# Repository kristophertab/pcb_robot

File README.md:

# PCB do robota
Płytka z mcu, optoizolowanym połączeniem uart, połączeniem st-link, kilkoma poziomami zasilania. Ma za zadanie sterować odczytywać dane z enkoderów i sterować, przez mostki, pracą silników
### Schemat

### PCB
Górna warstwa:

Dolna warstwa:

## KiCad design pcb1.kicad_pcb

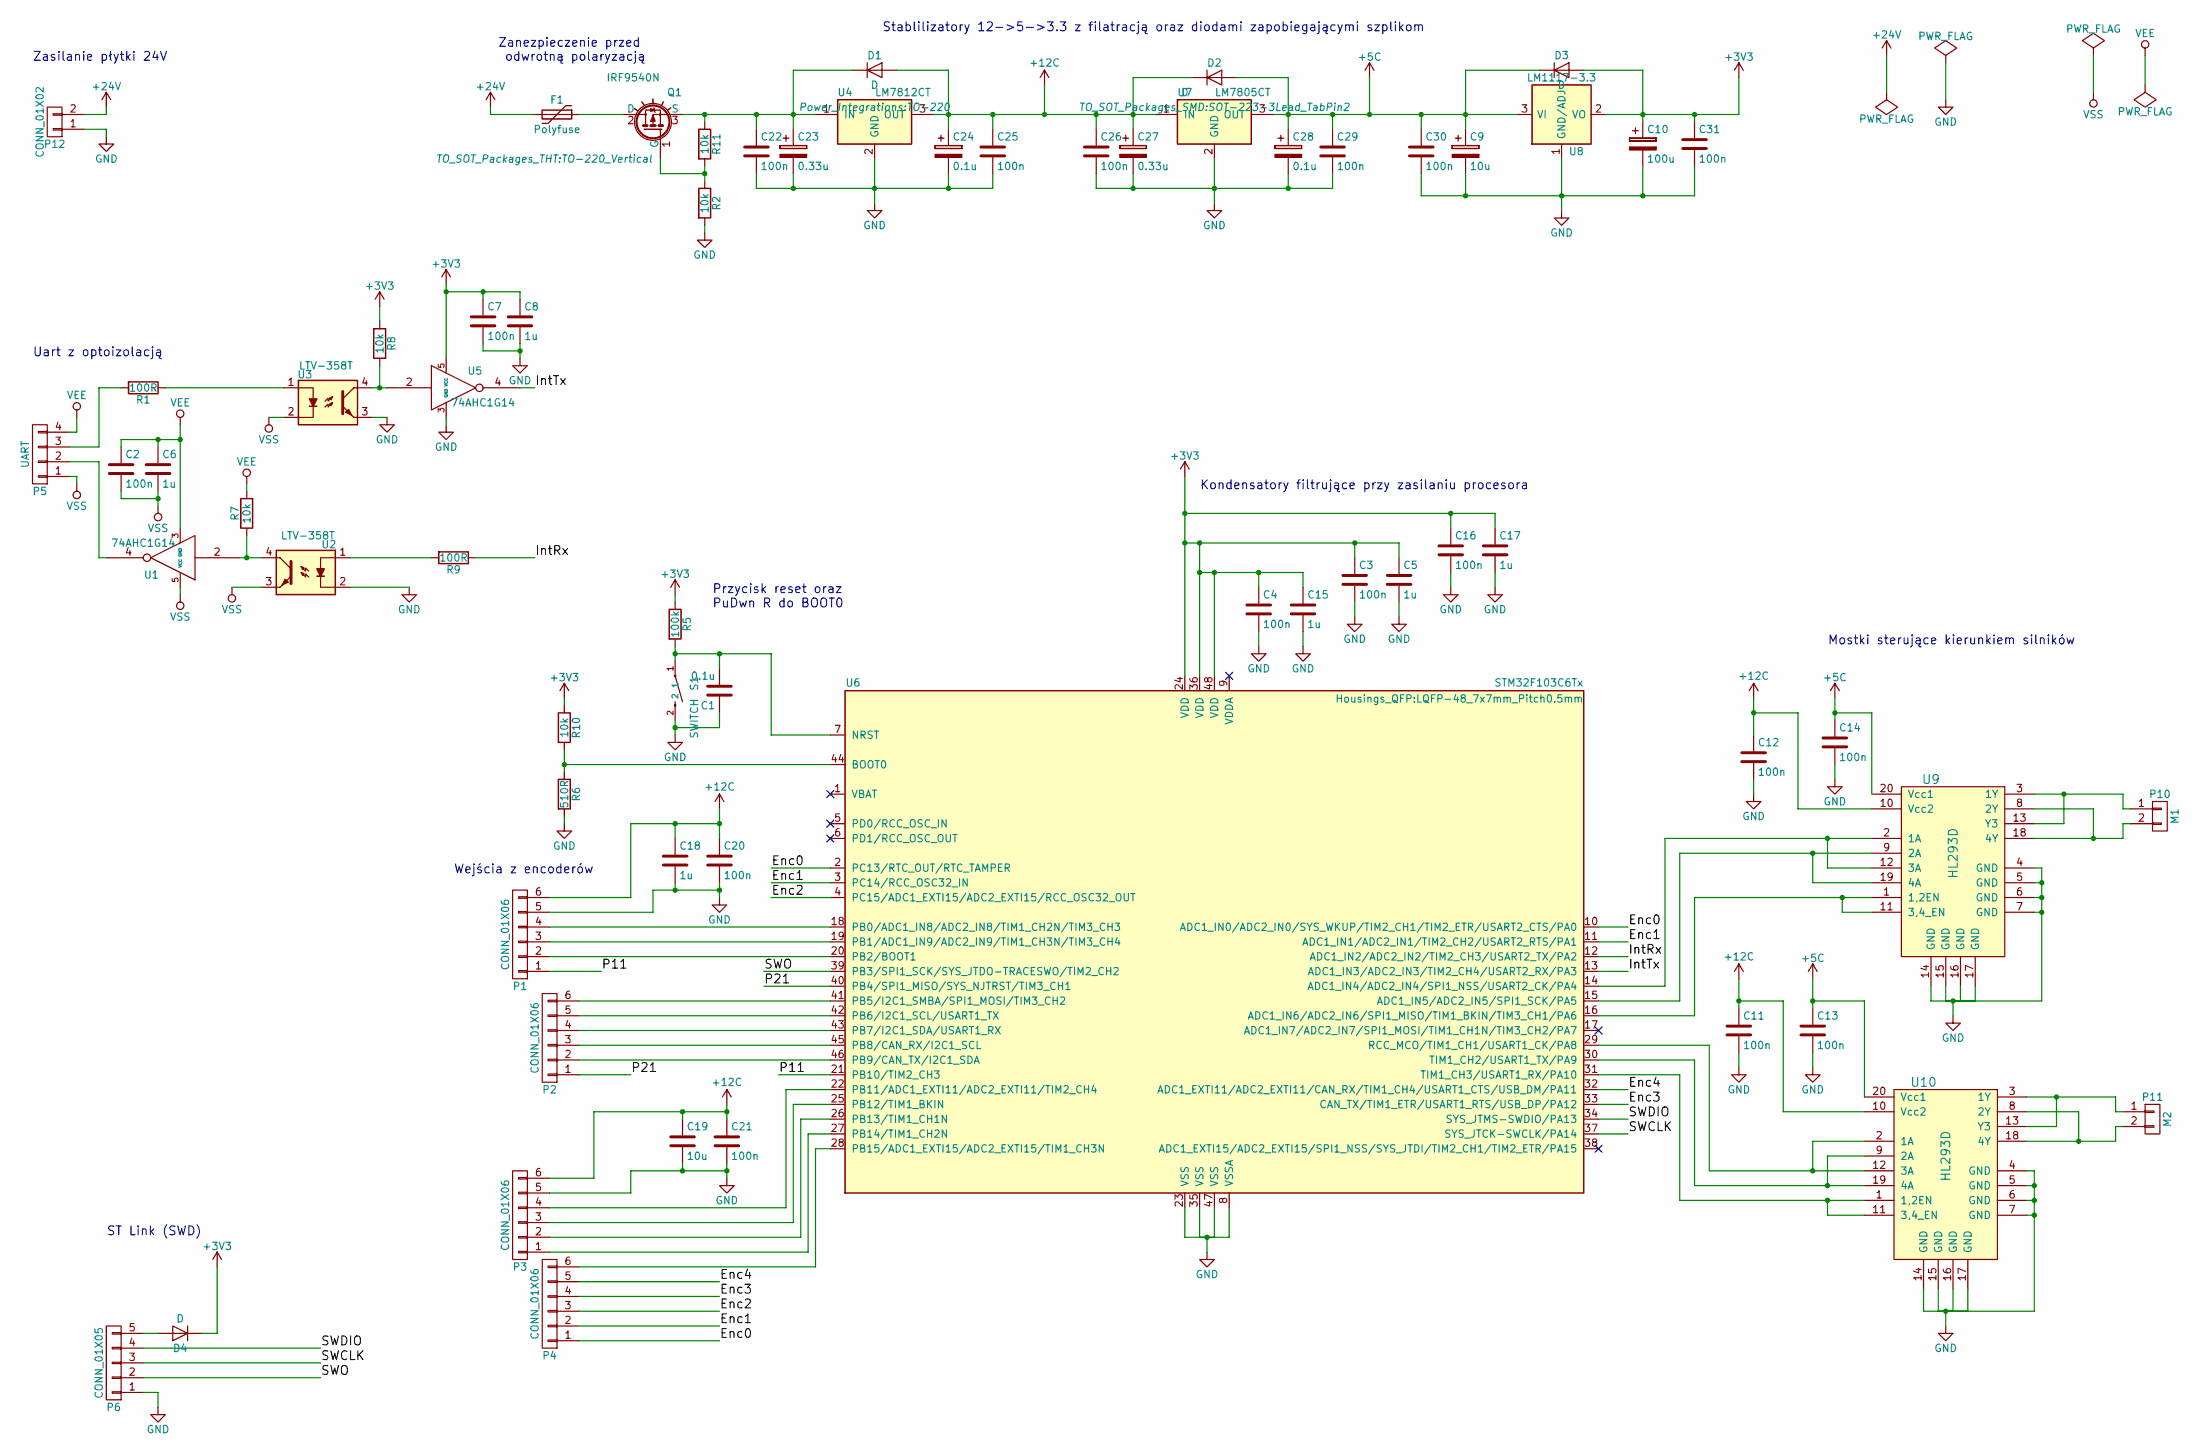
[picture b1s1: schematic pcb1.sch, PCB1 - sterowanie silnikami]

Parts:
C1, C24, C28: 0.1u; C_0805
C2, C3, C4, C7, C11, C12, C13, C14, C16, C20, C21, C22, C25, C26, C29, C30, C31: 100n; C_0805
C5, C6, C8, C15, C17, C18: 1u; C_0805
C9, C19: 10u; C_0805
C10: 100u; C_0805
C23, C27: 0.33u; C_0805
D1, D2, D3, D4: D; D_0805
F1: Polyfuse; SparkFun-PTC-1206
P1, P2, P3, P4: CONN_01X06; PINHEAD1-6
P5: UART; SparkFun-1X04
P6: CONN_01X05; SparkFun-1X05-1.27MM
P10: M1; bornier2
P11: M2; bornier2
P12: CONN_01X02; bornier2
Q1: IRF9540N; TO-220_Vertical
R1, R9: 100R; R_0805
R2, R7, R8, R10, R11: 10k; R_0805
R5: 100k; R_0805
R6: 510R; R_0805
S1: SWITCH; SW_SPST_TL3342
U1, U5: 74AHC1G14; SOT-353_SC-70-5
U2, U3: LTV-358T; SW_DIP_x2_W6.15mm_Slide_Omron_A6H
U4: LM7812CT; TO-220
U6: STM32F103C6Tx; LQFP-48_7x7mm_Pitch0.5mm
U7: LM7805CT; SOT-223-3Lead_TabPin2
U8: LM1117-3.3; SOT-223
U9, U10: HL293D; SOIC-20W_7.5x12.8mm_Pitch1.27mm

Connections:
+3V3: C3.1, C4.1, C5.1, C7.1, C8.1, C10.1, C15.1, C16.1, C17.1, C31.1, D3.2 (A), D4.1 (K), R5.1, R8.2, R10.1, U5.5 (VCC), U6.24 (VDD), U6.36 (VDD), U6.48 (VDD), U8.2 (VO), U8.4 (VO)
+5C: C9.1, C13.1, C14.1, C28.1, C29.1, C30.1, D2.2 (A), D3.1 (K), U7.3 (OUT), U8.3 (VI), U9.20 (Vcc1), U10.20 (Vcc1)
+12C: C11.1, C12.1, C18.1, C19.1, C20.1, C21.1, C24.1, C25.1, C26.1, C27.1, D1.2 (A), D2.1 (K), P1.6, P3.6, U4.3 (OUT), U7.1 (IN), U9.10 (Vcc2), U10.10 (Vcc2)
+24V: F1.2, P12.2
/Enc0: P4.1, U6.2 (PC13/RTC_OUT/RTC_TAMPER), U6.10 (ADC1_IN0/ADC2_IN0/SYS_WKUP/TIM2_CH1/TIM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)
/Enc1: P4.2, U6.3 (PC14/RCC_OSC32_IN), U6.11 (ADC1_IN1/ADC2_IN1/TIM2_CH2/USART2_RTS/P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)
/Enc2: P4.3, U6.4 (PC15/ADC1_EXTI15/ADC2_EXTI15/RCC_OSC32_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)
/Enc3: P4.4, U6.33 (CAN_TX/TIM1_ETR/USART1_RTS/USB_DP/PA12)
/Enc4: P4.5, U6.32 (ADC1_EXTI11/ADC2_EXTI11/CAN_RX/TIM1_CH4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)
/IntRx: R9.1, U6.12 (ADC1_IN2/ADC2_IN2/TIM2_CH3/USART2_TX/PA2)
/IntTx: U5.4, U6.13 (ADC1_IN3/ADC2_IN3/TIM2_CH4/USART2_RX/PA3)
/P11: P1.1, U6.21 (PB10/TIM2_CH3)
/P21: P2.1, U6.40 (PB4/SPI1_MISO/SYS_NJTRST/TIM3_CH1)
/SWCLK: P6.3, U6.37 (SYS_JTCK-SWCLK/PA14)
/SWDIO: P6.4, U6.34 (SYS_JTMS-SWDIO/PA13)
/SWO: P6.2, U6.39 (PB3/SPI1_SCK/SYS_JTDO-TRACESWO/TIM2_CH2)
GND: C1.1, C3.2, C4.2, C5.2, C7.2, C8.2, C9.2, C10.2, C11.2, C12.2, C13.2, C14.2, C15.2, C16.2, C17.2, C18.2, C19.2, C20.2, C21.2, C22.2, C23.2, C24.2, C25.2, C26.2, C27.2, C28.2, C29.2, C30.2, C31.2, P1.5, P3.5, P6.1, P12.1, R2.2, R6.2, S1.2, U2.2, U3.3, U4.2 (GND), U5.3 (GND), U6.8 (VSSA), U6.23 (VSS), U6.35 (VSS), U6.47 (VSS), U7.2 (GND), U8.1 (GND/ADJ), U9.4 (GND), U9.5 (GND), U9.6 (GND), U9.7 (GND), U9.14 (GND), U9.15 (GND), U9.16 (GND), U9.17 (GND), U10.4 (GND), U10.5 (GND), U10.6 (GND), U10.7 (GND), U10.14 (GND), U10.15 (GND), U10.16 (GND), U10.17 (GND)
unnamed: C1.2, R5.2, S1.1, U6.7 (NRST)
unnamed: C22.1, C23.1, D1.1 (K), Q1.3 (S), R11.1, U4.1 (IN)
unnamed: D4.2 (A), P6.5
unnamed: F1.1, Q1.2 (D)
unnamed: P1.2, U6.20 (PB2/BOOT1)
unnamed: P1.3, U6.19 (PB1/ADC1_IN9/ADC2_IN9/TIM1_CH3N/TIM3_CH4)
unnamed: P1.4, U6.18 (PB0/ADC1_IN8/ADC2_IN8/TIM1_CH2N/TIM3_CH3)
unnamed: P2.2, U6.46 (PB9/CAN_TX/I2C1_SDA)
unnamed: P2.3, U6.45 (PB8/CAN_RX/I2C1_SCL)
unnamed: P2.4, U6.43 (PB7/I2C1_SDA/USART1_RX)
unnamed: P2.5, U6.42 (PB6/I2C1_SCL/USART1_TX)
unnamed: P2.6, U6.41 (PB5/I2C1_SMBA/SPI1_MOSI/TIM3_CH2)
unnamed: P3.1, U6.27 (PB14/TIM1_CH2N)
unnamed: P3.2, U6.26 (PB13/TIM1_CH1N)
unnamed: P3.3, U6.25 (PB12/TIM1_BKIN)
unnamed: P3.4, U6.22 (PB11/ADC1_EXTI11/ADC2_EXTI11/TIM2_CH4)
unnamed: P4.6, U6.28 (PB15/ADC1_EXTI15/ADC2_EXTI15/TIM1_CH3N)
unnamed: P5.2, U1.4
unnamed: P5.3, R1.2
unnamed: P10.1, U9.3 (1Y), U9.13 (Y3)
unnamed: P10.2, U9.8 (2Y), U9.18 (4Y)
unnamed: P11.1, U10.3 (1Y), U10.13 (Y3)
unnamed: P11.2, U10.8 (2Y), U10.18 (4Y)
unnamed: Q1.1 (G), R2.1, R11.2
unnamed: R1.1, U3.1
unnamed: R7.1, U1.2, U2.4
unnamed: R8.1, U3.4, U5.2
unnamed: R9.2, U2.1
unnamed: R6.1, R10.2, U6.44 (BOOT0)
unnamed: U6.14 (ADC1_IN4/ADC2_IN4/SPI1_NSS/USART2_CK/PA4), U9.2 (1A), U9.12 (3A)
unnamed: U6.15 (ADC1_IN5/ADC2_IN5/SPI1_SCK/PA5), U9.9 (2A), U9.19 (4A)
unnamed: U6.16 (ADC1_IN6/ADC2_IN6/SPI1_MISO/TIM1_BKIN/T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), U9.1 (1,2EN), U9.11 (3,4_EN)
unnamed: U6.31 (TIM1_CH3/USART1_RX/PA10), U10.1 (1,2EN), U10.11 (3,4_EN)
unnamed: U6.29 (RCC_MCO/TIM1_CH1/USART1_CK/PA8), U10.2 (1A), U10.12 (3A)
unnamed: U6.30 (TIM1_CH2/USART1_TX/PA9), U10.9 (2A), U10.19 (4A)
VEE: C2.1, C6.1, P5.4, R7.2, U1.3 (GND)
VSS: C2.2, C6.2, P5.1, U1.5 (VCC), U2.3, U3.2

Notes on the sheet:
Stablilizatory 12->5->3.3 z filatracją oraz diodami zapobiegającymi szplikom
Zanezpieczenie przed odwrotną polaryzacją
Mostki sterujące kierunkiem silników
Uart z optoizolacją
ST Link (SWD)
Zasilanie płytki 24V
Kondensatory filtrujące przy zasilaniu procesora
Wejścia z encoderów
Przycisk reset oraz PuDwn R do BOOT0

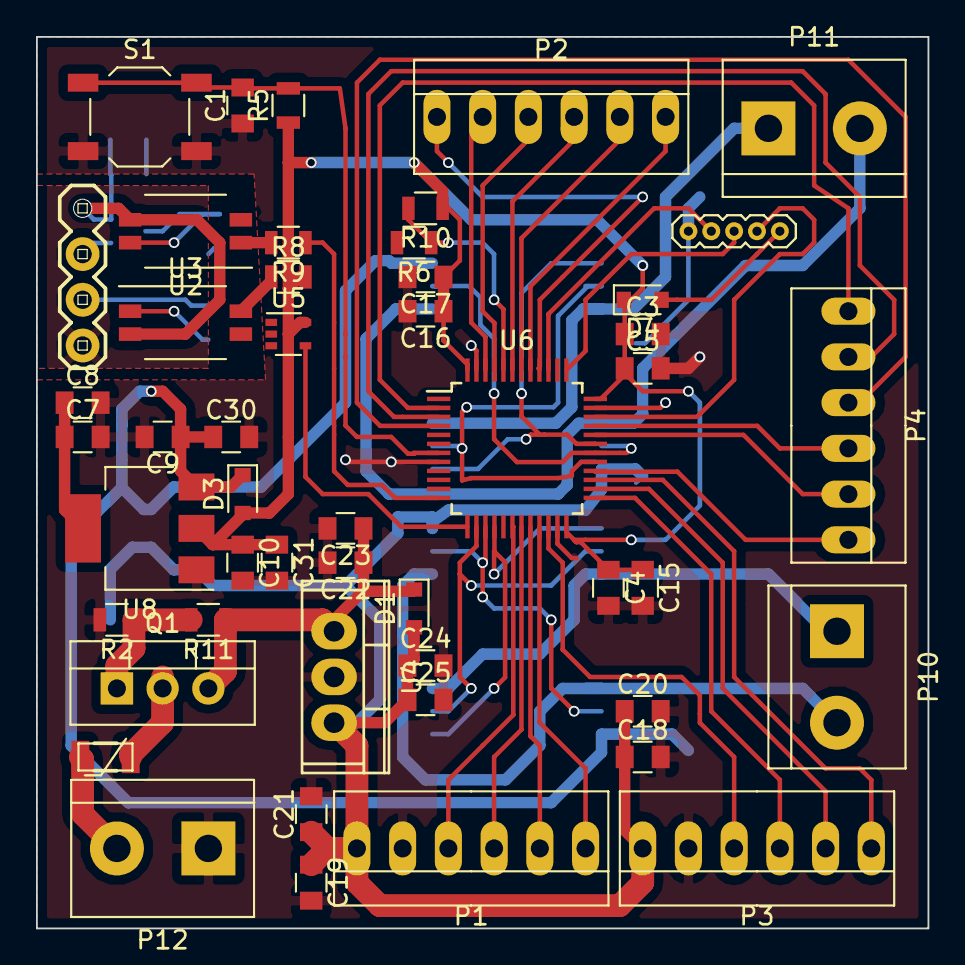
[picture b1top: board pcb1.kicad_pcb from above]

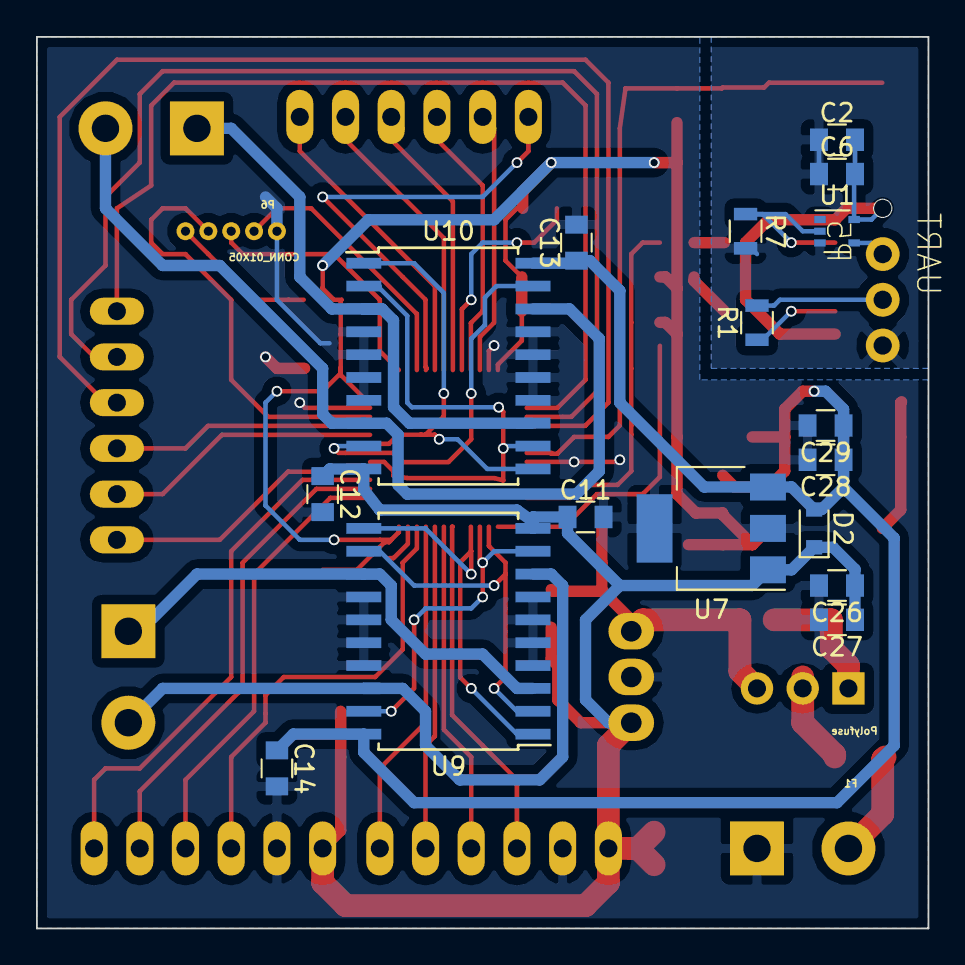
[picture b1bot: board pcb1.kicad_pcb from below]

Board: 2 copper layers, 49.5 x 49.5 mm, 66 parts (17 on the bottom side), 54 nets.

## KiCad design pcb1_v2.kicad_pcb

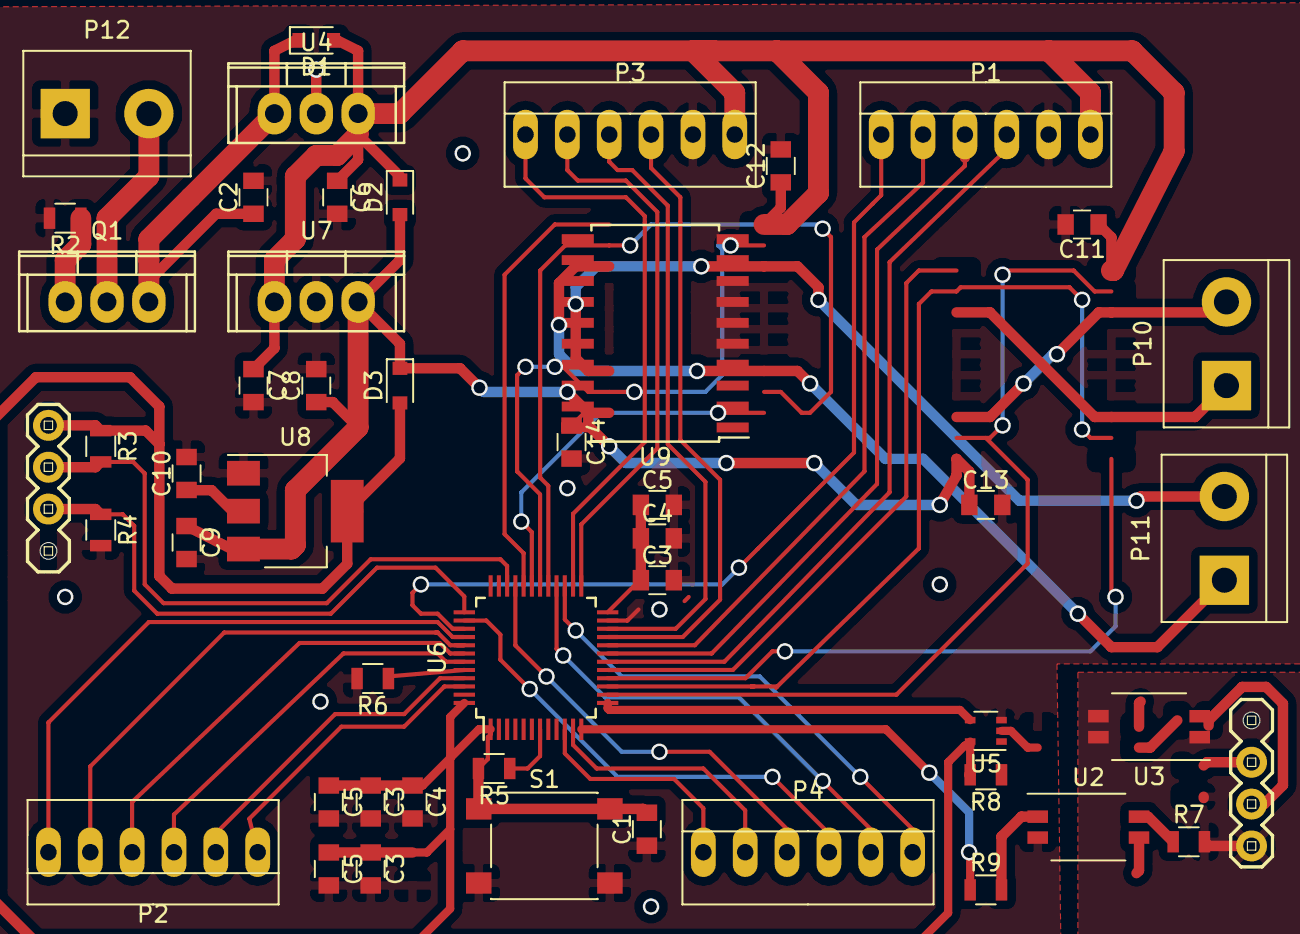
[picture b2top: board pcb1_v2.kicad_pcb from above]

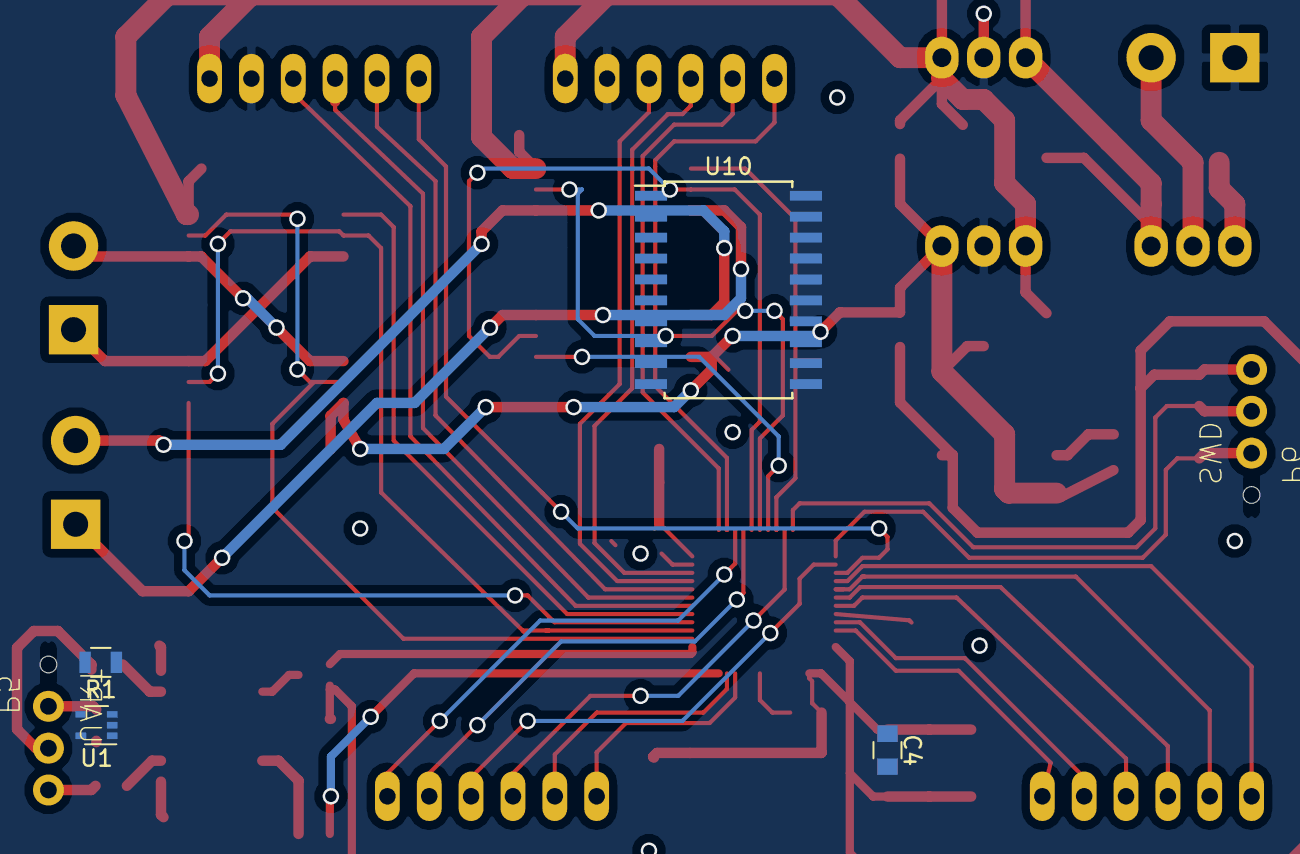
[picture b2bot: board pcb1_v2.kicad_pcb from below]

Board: 2 copper layers, 53 parts (4 on the bottom side), 52 nets.

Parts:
C1, C6, C8: 0.1u; C_0805
C2, C7: 0.33u; C_0805
C3, C3#2, C3#3, C4, C4#2, C4#3, C11, C12, C13, C14: 100n; C_0805
C5, C5#2, C5#3: 4.7u; C_0805
C9: 10u; C_0805
C10: 100u; C_0805
D1, D2, D3: D; D_0805
P1, P2, P3, P4: CONN_01X06; PINHEAD1-6
P5: UART; SparkFun-1X04
P6: SWD; SparkFun-1X04
P10: M1; bornier2
P11: M2; bornier2
P12: CONN_01X02; bornier2
Q1: IRF9540N; TO-220
R1, R3, R4, R5, R7, R8, R9: 100k; R_0805
R2: 1k; R_0805
R6: 10k; R_0805
S1: SWITCH; SW_SPST_PTS645
U1, U5: 74AHC1G14; SOT-353_SC-70-5
U2, U3: LTV-358T; SW_DIP_x2_W6.15mm_Slide_Omron_A6H
U4: LM7812CT; TO-220
U6: STM32F030C6Tx; LQFP-48_7x7mm_Pitch0.5mm
U7: LM7805CT; TO-220
U8: LM1117-3.3; SOT-223
U9, U10: HL293D; SOIC-20W_7.5x12.8mm_Pitch1.27mm

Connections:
+3V3: C1.2, C3.1, C3#2.1, C3#3.1, C4.1, C4#2.1, C4#3.1, C5.1, C5#2.1, C5#3.1, C10.1, D3.2, P6.4, R3.1, R5.2, R8.2, S1.1, U5.5, U6.1, U6.24, U6.48, U8.2, U8.4
+5C: C8.1, C9.1, C13.1, C14.1, D2.2, D3.1, U7.3, U8.3, U9.20, U10.20
+12C: C6.1, C7.1, C11.1, C12.1, D1.2, D2.1, P1.6, P3.6, U4.3, U7.1, U9.10, U10.10
+24V: P12.2, Q1.2
/Enc0: P4.1, U6.10
/Enc1: P4.2, U6.11
/Enc2: P4.3, U6.33
/Enc3: P4.4, U6.38
/IntRx: R9.1, U6.12
/IntTx: U5.4, U6.13
/SWCLK: P6.2, R4.1, U6.37
/SWDIO: P6.3, R3.2, U6.34
GND: C1.1, C2.2, C3.2, C3#2.2, C3#3.2, C4.2, C4#2.2, C4#3.2, C5.2, C5#2.2, C5#3.2, C6.2, C7.2, C8.2, C9.2, C10.2, C11.2, C12.2, C13.2, C14.2, P1.5, P3.5, P5.1, P6.1, P12.1, R2.2, R4.2, R6.2, S1.2, U1.5, U2.2, U2.3, U3.2, U3.3, U4.2, U5.3, U6.23, U6.47, U7.2, U8.1, U9.4, U9.5, U9.6, U9.7, U9.14, U9.15, U9.16, U9.17, U10.4, U10.5, U10.6, U10.7, U10.14, U10.15, U10.16, U10.17
unnamed: C2.1, D1.1, Q1.3, U4.1
unnamed: P1.1, U6.39
unnamed: P1.2, U6.20
unnamed: P1.3, U6.19
unnamed: P1.4, U6.18
unnamed: P2.1, U6.46
unnamed: P2.2, U6.45
unnamed: P2.3, U6.43
unnamed: P2.4, U6.42
unnamed: P2.5, U6.41
unnamed: P2.6, U6.40
unnamed: P3.1, U6.26
unnamed: P3.2, U6.25
unnamed: P3.3, U6.22
unnamed: P3.4, U6.21
unnamed: P4.5, U6.28
unnamed: P4.6, U6.27
unnamed: P5.2, U1.4
unnamed: P5.3, R1.2
unnamed: P10.1, U9.3, U9.8
unnamed: P10.2, U9.13, U9.18
unnamed: P11.1, U10.3, U10.8
unnamed: P11.2, U10.13, U10.18
unnamed: Q1.1, R2.1
unnamed: R1.1, U3.1
unnamed: R5.1, U6.7
unnamed: R6.1, U6.44
unnamed: R7.1, U1.2, U2.4
unnamed: R8.1, U3.4, U5.2
unnamed: R9.2, U2.1
unnamed: U6.14, U9.2, U9.12
unnamed: U6.15, U9.9, U9.19
unnamed: U6.16, U9.1
unnamed: U6.17, U9.11
unnamed: U6.31, U10.1
unnamed: U6.32, U10.11
unnamed: U6.29, U10.2, U10.12
unnamed: U6.30, U10.9, U10.19
VEE: P5.4, R7.2, U1.3

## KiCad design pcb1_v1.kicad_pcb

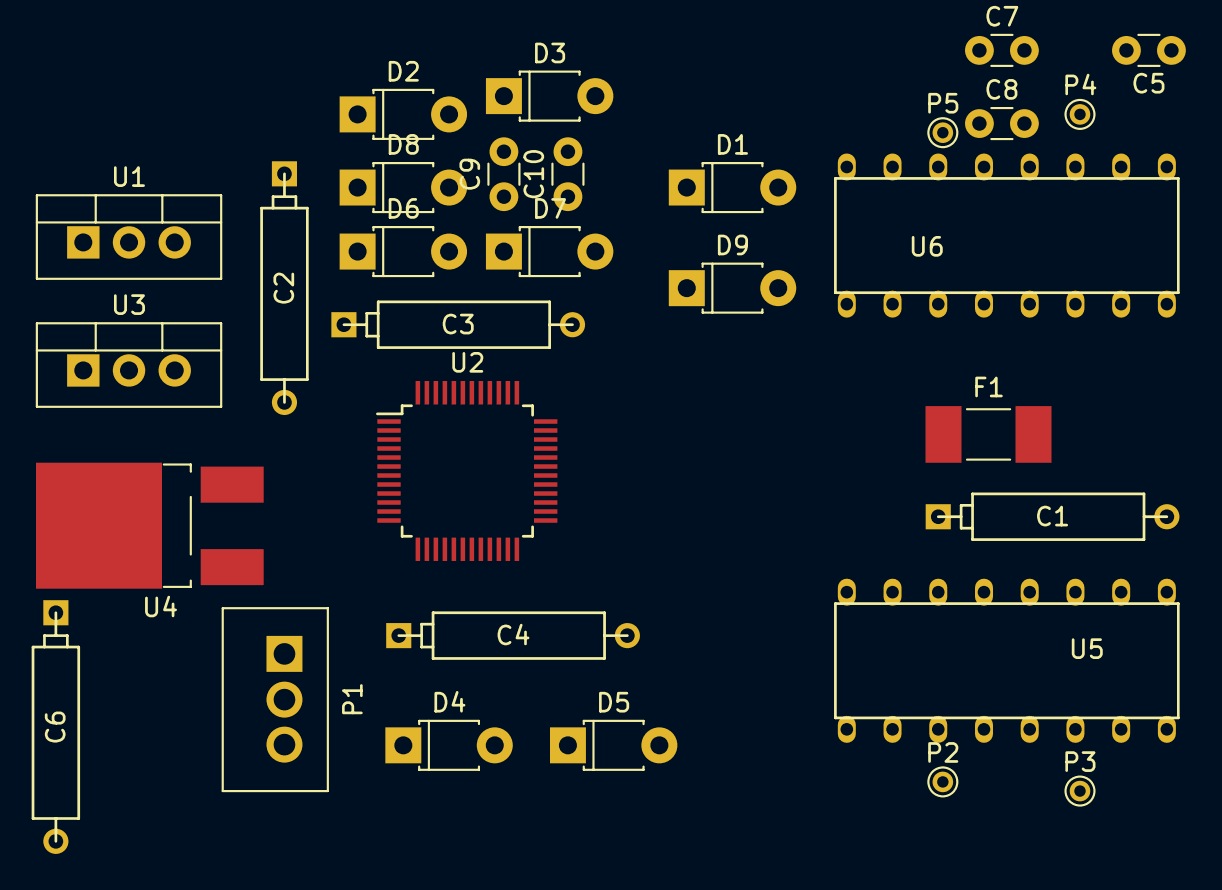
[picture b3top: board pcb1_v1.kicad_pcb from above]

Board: 2 copper layers, 31 parts (0 on the bottom side), 17 nets, no tracks yet.

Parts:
C1, C3: 0.33u; CP5
C2, C4: 0.1u; CP5
C5: 0.1u; C_Disc_D3.0mm_W1.6mm_P2.50mm
C6: 2.2u; CP5
C7, C8, C9, C10: 100n; C_Disc_D3.0mm_W1.6mm_P2.50mm
D1: D_Zener; D_T-1_P5.08mm_Horizontal
D2, D3, D4, D5, D6, D7, D8, D9: D; D_T-1_P5.08mm_Horizontal
F1: Fuse; Fuse_CB61F
P1: UART GND, Tx, Rx; Wafer_Vertical10x5.8x7RM2.5-3
P2: M1 A; PINTST
P3: M1 B; PINTST
P4: M2 A; PINTST
P5: M2 B; PINTST
U1: LM7812; TO-220_Vertical
U2: STM32F030C6Tx; LQFP-48_7x7mm_Pitch0.5mm
U3: 7805; TO-220_Vertical
U4: LF33ABDT-TR; TO-252-2Lead
U5, U6: HL293D

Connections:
/3.3V: C6.1, U2.1, U2.9, U2.24, U2.48, U4.3
/5V: C4.1, C5.1, C9.1, C10.1, U4.1, U5.16, U6.16
/12V: C2.1, C3.1, C7.1, C8.1, D2.1, D4.1, D6.1, D8.1, U5.8, U6.8
GND: C1.2, C2.2, C3.2, C4.2, C5.2, C6.2, C7.2, C8.2, C9.2, C10.2, D1.2, D3.2, D5.2, D7.2, D9.2, P1.1, U2.8, U2.23, U2.47, U4.2, U5.4, U5.5, U5.9, U5.12, U5.13, U6.4, U6.5, U6.9, U6.12, U6.13
unnamed: C1.1, D1.1, F1.1
unnamed: D2.2, D3.1, P2.1, U5.3
unnamed: D4.2, D5.1, P3.1, U5.6
unnamed: D6.2, D7.1, P4.1, U6.3
unnamed: D8.2, D9.1, P5.1, U6.6
unnamed: P1.2, U2.12
unnamed: P1.3, U2.13
unnamed: U2.14, U5.2
unnamed: U2.15, U5.7
unnamed: U2.16, U5.1
unnamed: U2.17, U6.1
unnamed: U2.29, U6.2
unnamed: U2.30, U6.7

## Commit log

2017-03-11 almost ready schemat pcb started
2017-04-02 almoast half ready ;)
2017-04-28 final
